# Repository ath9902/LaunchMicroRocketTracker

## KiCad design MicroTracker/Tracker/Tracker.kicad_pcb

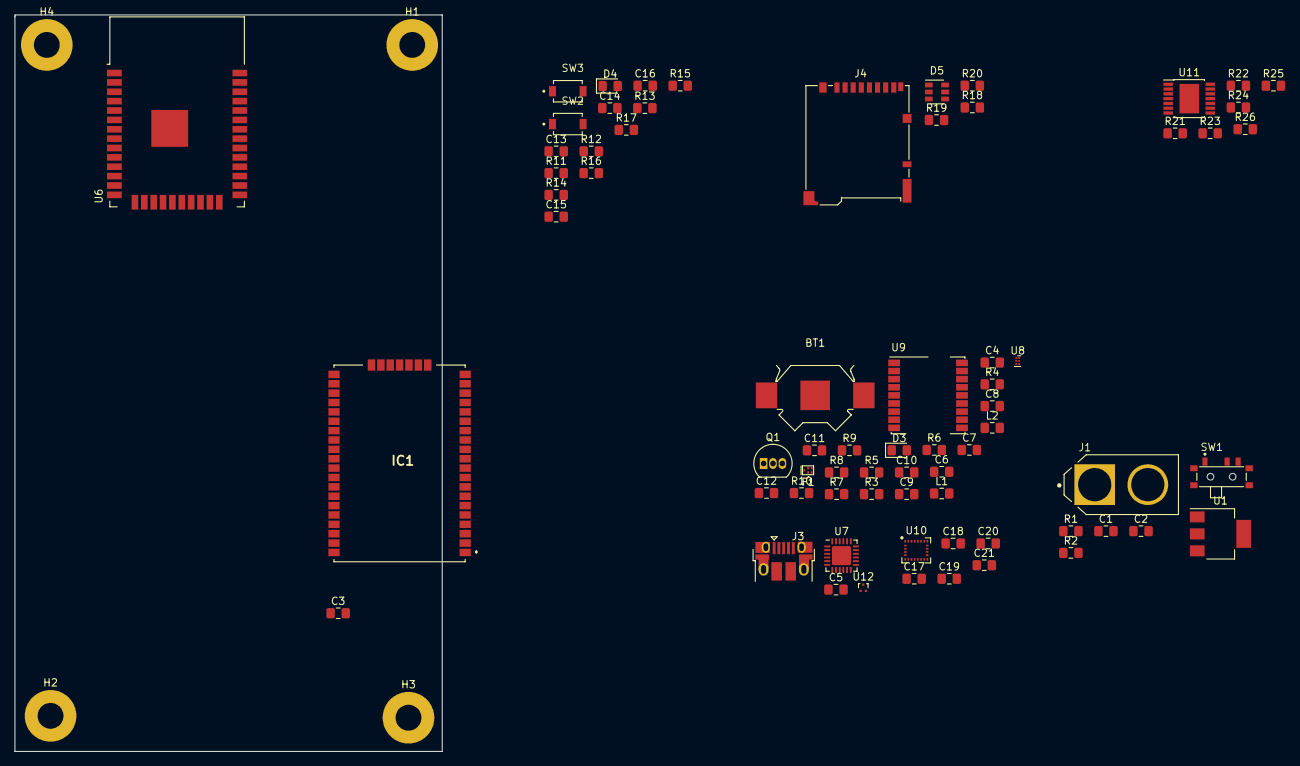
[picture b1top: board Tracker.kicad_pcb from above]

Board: 2 copper layers, 57.9 x 99.8 mm, 74 parts (0 on the bottom side), 47 nets, no tracks yet.

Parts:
BT1: Battery_Cell; Keystone_3030_1x10mm-CoinCell
C1, C3: 100nF; C_0805_2012Metric_Pad1.15x1.40mm_HandSolder
C2, C15: 10uF; C_0805_2012Metric_Pad1.15x1.40mm_HandSolder
C4: 56p; C_0805_2012Metric_Pad1.15x1.40mm_HandSolder
C5, C17, C18, C19: C; C_0805_2012Metric_Pad1.15x1.40mm_HandSolder
C6: 1u; C_0805_2012Metric_Pad1.15x1.40mm_HandSolder
C7: 120p; C_0805_2012Metric_Pad1.15x1.40mm_HandSolder
C8: 1n; C_0805_2012Metric_Pad1.15x1.40mm_HandSolder
C9: 100p; C_0805_2012Metric_Pad1.15x1.40mm_HandSolder
C10: 2.2u; C_0805_2012Metric_Pad1.15x1.40mm_HandSolder
C11: 100n; C_0805_2012Metric_Pad1.15x1.40mm_HandSolder
C12: 120pF; C_0805_2012Metric_Pad1.15x1.40mm_HandSolder
C13, C14, C16, C21: 0.1uF; C_0805_2012Metric_Pad1.15x1.40mm_HandSolder
C20: 10nF; C_0805_2012Metric_Pad1.15x1.40mm_HandSolder
D3, D4: LED; LED_0805_2012Metric_Pad1.15x1.40mm_HandSolder
D5: ESDA6V1BC6; SOT-23-6
F1: B4327; Filter_1411-5_1.4x1.1mm
H1, H2, H3, H4: MountingHole_Pad; MountingHole_3.5mm_Pad
IC1: RN2483A-I_RM105; RN2483AIRM104
J1: Screw_Terminal_01x02; AMASS_XT60-M
J3: USB_A; USB_Micro-B_Amphenol_10103594-0001LF_Horizontal
J4: Micro_SD_Card; microSD_HC_Hirose_DM3BT-DSF-PEJS
L1: 56n; L_0805_2012Metric_Pad1.15x1.40mm_HandSolder
L2: 6.8n; L_0805_2012Metric_Pad1.15x1.40mm_HandSolder
Q1: BC237; TO-92_Inline
R1, R8, R16, R17: 10k; R_0805_2012Metric_Pad1.15x1.40mm_HandSolder
R2: 3.3k; R_0805_2012Metric_Pad1.15x1.40mm_HandSolder
R3, R5, R9, R10: 0; R_0805_2012Metric_Pad1.15x1.40mm_HandSolder
R4: 330; R_0805_2012Metric_Pad1.15x1.40mm_HandSolder
R6: 100k; R_0805_2012Metric_Pad1.15x1.40mm_HandSolder
R7, R19, R21, R22, R23, R24, R25, R26: R; R_0805_2012Metric_Pad1.15x1.40mm_HandSolder
R11, R13, R18: 12k; R_0805_2012Metric_Pad1.15x1.40mm_HandSolder
R12, R14: 470; R_0805_2012Metric_Pad1.15x1.40mm_HandSolder
R15: 220; R_0805_2012Metric_Pad1.15x1.40mm_HandSolder
R20: 100; R_0805_2012Metric_Pad1.15x1.40mm_HandSolder
SW1: SW_SPDT; SW_MLL1200S
SW2, SW3: SW_Push; SW_TL1015AF160QG
U1: LD1117S33TR_SOT223; SOT-223-3_TabPin2
U6: ESP32-WROOM-32D; ESP32-WROOM-32
U7: CP2104; QFN-24-1EP_4x4mm_P0.5mm_EP2.6x2.6mm
U8: BGA725L6; TSNP-6_0.8x0.7mm_P0.4mm
U9: TESEO-LIV3F; TESEO_LIV3F_SMD
U10: LSM9DS1; LGA-24L_3x3.5mm_P0.43mm
U11: BTS7004-1EPP; Infineon_PG-TSDSO-14-22
U12: TPD2EUSB30; Texas_DRT-3

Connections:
9DofSCL: R17.2, U6.36, U10.2
9DofSDA: R16.2, U6.33, U10.4
+3V3: C2.1, C3.1, C5.1, C9.1, C11.1, C15.1, C16.1, C17.1, C18.1, C19.1, IC1.12, IC1.34, J4.4, R4.1, R11.1, R13.1, R16.1, R17.1, R18.1, R19.2, U1.2, U6.2, U7.5, U7.6, U7.7, U9.7, U9.8, U10.1, U10.3, U10.7, U10.8, U10.22, U10.23
+7.5V: C1.1, R1.1, U1.3
+BATT: BT1.1, U9.6
/Charges/charge1Sense: R25.2, R26.1
/Charges/charge2Sense: R23.2, R24.1
/GPS/ANT_OFF: R7.1, R8.1, U8.6, U9.13
/GPS/RF_IN: C12.1, R10.1, U9.11
/GPS/VCC_RF: C8.1, R9.1, U8.2, U9.14
En: C13.1, R11.2, R12.1, U6.3
Flash: C14.1, R13.2, R14.1, U6.25
GND: BT1.2, C1.2, C2.2, C3.2, C4.2, C5.2, C6.2, C8.2, C9.2, C11.2, C13.2, C14.2, C15.2, C16.2, C17.2, C18.2, C19.2, C20.2, C21.2, D5.2, D5.5, F1.2, F1.3, F1.5, H1.1, H2.1, H3.1, H4.1, IC1.1, IC1.8, IC1.20, IC1.21, IC1.22, IC1.24, IC1.26, IC1.27, IC1.28, IC1.33, IC1.41, IC1.47, J1.1, J3.4, J4.6, J4.9, Q1.3, R2.2, R8.2, R15.2, R21.2, R22.2, SW2.2, SW3.2, U1.1, U6.1, U6.15, U6.38, U6.39, U7.2, U7.25, U8.1, U8.4, U9.1, U9.10, U9.12, U10.14, U10.15, U10.16, U10.17, U10.18, U10.19, U10.20, U12.3
GPS_RX: U6.18, U9.3
GPS_TX: U6.17, U9.2
unnamed: C4.1, L1.2, R3.1
unnamed: C6.1, R3.2
unnamed: C7.1, L2.2
unnamed: C7.2, L1.1, R5.1
unnamed: C10.1, R6.1, R9.2
unnamed: C12.2, F1.4
unnamed: C20.1, U10.21
unnamed: C21.1, U10.24
unnamed: J1.2, SW1.2
unnamed: D3.1, Q1.1
unnamed: D3.2, R4.2
unnamed: D4.1, R15.1
unnamed: D5.3, J4.5, R20.1
unnamed: F1.1, U8.3
unnamed: J3.2, U7.3, U12.2
unnamed: J3.3, U7.4, U12.1
unnamed: J4.1, R19.1
unnamed: J4.8, R18.2
unnamed: L2.1, U8.5
unnamed: R5.2, R10.2
unnamed: R12.2, SW2.1
unnamed: R14.2, SW3.1
unnamed: U11.8, U11.9, U11.10, U11.12, U11.13, U11.14
SD_CLK: R20.2, U6.30
SD_CS: D5.6, J4.2, U6.29
SD_MISO: D5.1, J4.7, U6.37
SD_MOSI: D5.4, J4.3, U6.31
StatusLed: D4.2, U6.23
Transceiver_RX: IC1.6, IC1.7, U6.28
USB_RXD0: U6.35, U7.20
USB_TXD0: U6.34, U7.21
v_bat_measure: R1.2, R2.1, U6.16

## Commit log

2020-06-25 init project
2020-07-07 added more sensors
2020-07-07 added connections
2020-07-08 started working on gps
2020-07-08 gps finished
2020-07-08 added charges
2020-07-09 assigned parts
2020-07-11 added more parts and lib
2020-07-12 fixed errors
